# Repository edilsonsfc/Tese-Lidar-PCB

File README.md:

# Circuit Board (PCB) of Master's Thesis
This repository contains the circuit board project and supplementary materials related to my master's thesis.

## Table of Contents
- [Introduction](#introduction)
- [PCB](#pcb)
- [How to Use](#how-to-use)
- [Citation](#citation)

## Introduction
My master's thesis, titled "Three-dimensional mapping of an unknown environment based on a 2D laser measurement" explores the development of a low-cost 3D mapping system capable of generating a point cloud of an indoor environment and performing path planning. The work presented in this repository supports the findings and experiments conducted during the research process.
- [Hardware Structure](https://github.com/edilsonsfc/Tese-Lidar-Structure)
- [Printed Circuit Board](https://github.com/edilsonsfc/Tese-Lidar-PCB)
- [Control and Data Processing Algorithm](https://github.com/edilsonsfc/Tese-Lidar-Code)
- [Graphical User Interface](https://github.com/edilsonsfc/Tese-Lidar-GUI)

## PCB
This repository contains a collection of [...].

## How to Use

Feel free to explore and incorporate these models into your research or projects. Don't forget to cite this repository if you use the 3D models in your work.

## Citation
If you use the any material from this repository in your research or projects, please cite my master's thesis and this repository as follows:

- Master's Thesis: Ferreira, E. "Three-dimensional mapping of an unknown environment based on a 2D laser measurement" Instituto Politécnico de Bragança, 2023.
- Repository: https://github.com/edilsonsfc/Tese-Lidar-PCB

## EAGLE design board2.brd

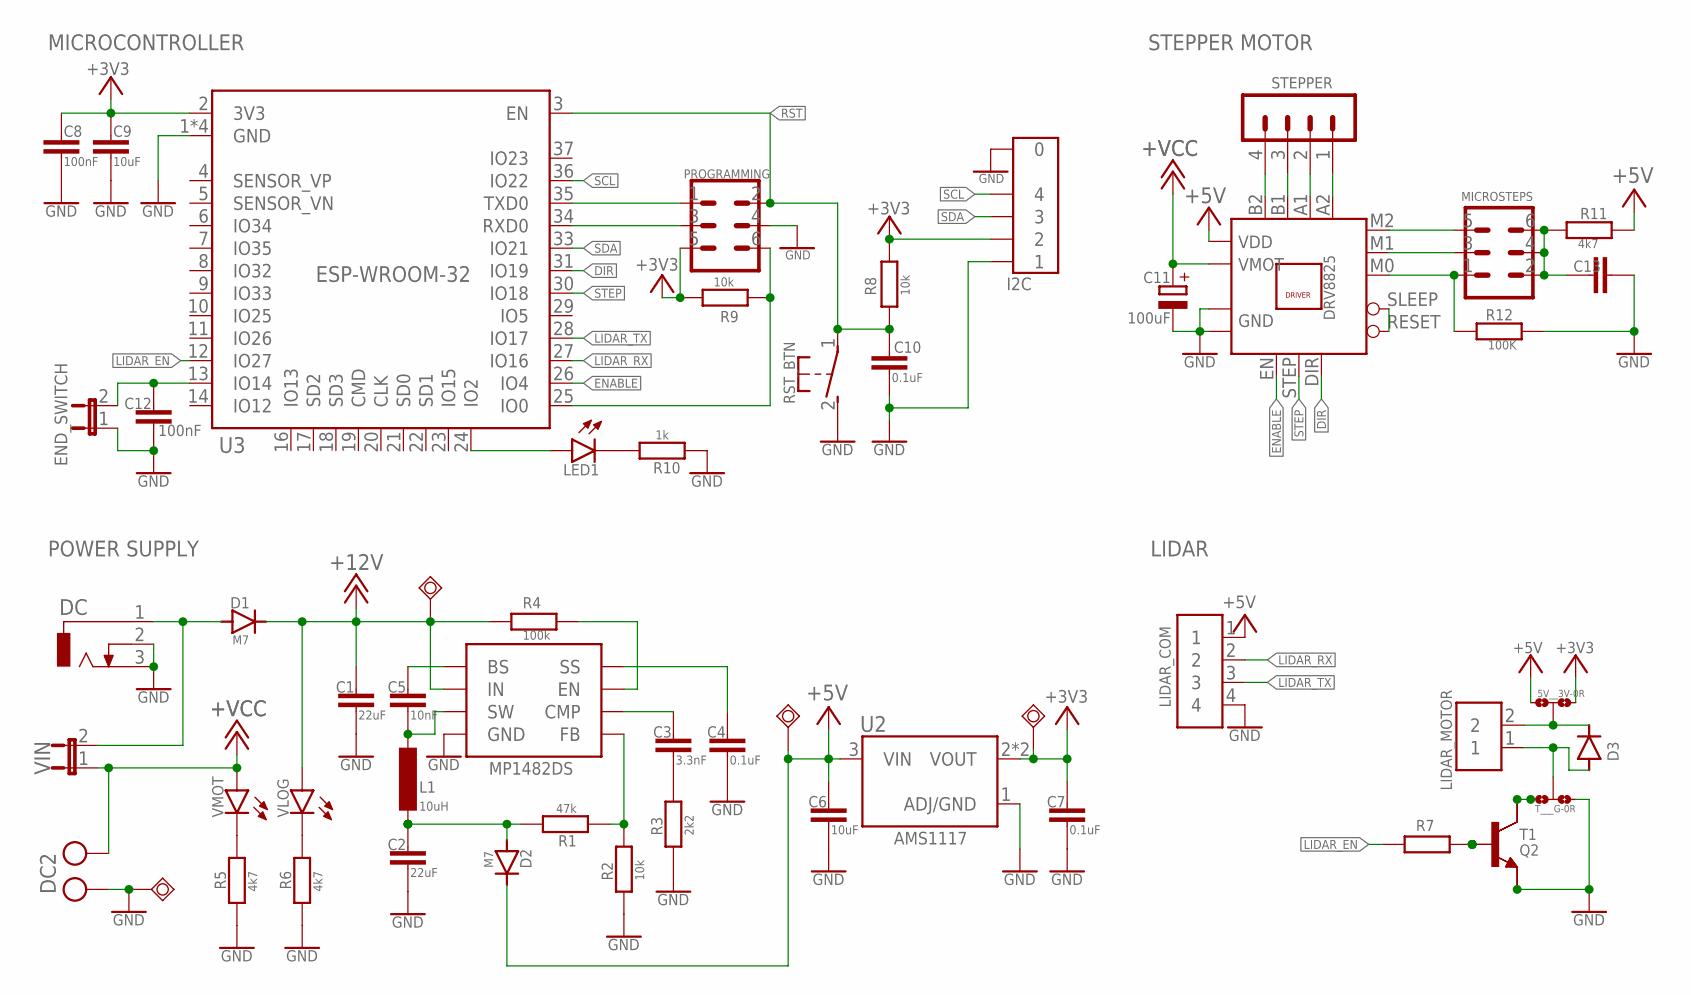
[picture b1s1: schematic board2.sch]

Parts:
3V3, 5V, 12V: TPSQTP07R; TP07R
5V__3V: 0R-JUMPA; A0R-JMP
C1, C2: 22uF; C1210K
C3: 3.3nF; C0805K
C4, C10: 0.1uF; C0805K
C5: 10nF; C0805K
C6, C9: 10uF; C1210K
C7: 0.1uF; C1210K
C8, C12: 100nF; C0805K
C11: 100uF; E3,5-8
C13: C-EUC0805K; C0805K
D1, D2, D3: M7; DO-214AC
DC: DCJ0202
DC2: DC2; AK500/2-H
DRIVER: DRV8825_PCB
DRV8825: DRV8825_H
END_SWITCH: END_SWITCH; JP1
GND: TPSQTP07R; TP07R
I2C: SM04B-SRSS-TB(LF)(SN); JST_SM04B-SRSS-TB(LF)(SN)
L1: 10uH; L5650M
LED1: 0; CHIP-LED0805
LIDAR_COM: 4PIN; B4B-PH-K-S
LIDAR_MOTOR: 2PIN; B2B-PH-K-S
MICROSTEPS: MicroSteps; MA03-2
PROGRAMMING: Programming; MA03-2
Q2: BC846ALT1SMD; SOT23
R1: 47k; R0805W
R2, R8, R9: 10k; R0805W
R3: 2k2; R0805W
R4: 100k; R0805W
R5, R6, R11: 4k7; R0805W
R7: R; R0805W
R10: 1k; R0805W
R12: 100K; R0805W
RST_BTN: DTSM-3
STEPPER: Stepper; MA04-1
T1: BD139_BCXXX; TO126+TO92
T___G: 0R-JUMPB; B0R-JMP
U1: MP1482DS; SOIC127P600X175-8N
U2: AMS1117; SOT229P700X180-4N
U3: ESP-WROOM-32
VIN: JUMPER; JP1
VLOG: 00; CHIP-LED0805
VMOT: 00; CHIP-LED0805

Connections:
+3V3: 3V3.TP, 5V__3V.1, 5V__3V.2, C7.1, C8.1, C9.1, D3.C, I2C.2, LIDAR_MOTOR.2, PROGRAMMING.5, R8.1, R9.2, U2.2 (VOUT), U2.4 (VOUT), U3.2 (3V3)
+5V: 5V.TP, 5V__3V.3, C6.2, D2.C, DRV8825.FAULT (VDD), LIDAR_COM.1, R11.2, U2.3 (VIN)
+12V: 12V.TP, C1.2, D1.C, R4.1, U1.2 (IN), VLOG.A
+VCC: C11.+, DC2.2, DRV8825.VMOT, DRV8825.VMOT1 (VMOT), VIN.1, VMOT.A
A1: DRV8825.A1, STEPPER.2
A2: DRV8825.A2, STEPPER.1
B1: DRV8825.B1, STEPPER.3
B2: DRV8825.B2, STEPPER.4
BS: C5.2, U1.1 (BS)
CMP: C3.2, U1.6 (CMP)
DIR: DRV8825.DIR, U3.31 (IO19)
EN: R4.2, U1.7 (EN)
ENABLE: DRV8825.EN, U3.26 (IO4)
END_SW: C12.2, END_SWITCH.2, U3.13 (IO14)
GND: C1.1, C2.2, C4.1, C6.1, C7.2, C8.2, C9.2, C10.2, C11.-, C12.1, C13.2, DC.2, DC.3, DC2.1, DRV8825.GND, DRV8825.GND1 (GMOT), END_SWITCH.1, GND.TP, I2C.1, I2C.S1 (0), I2C.S2 (0), LIDAR_COM.4, PROGRAMMING.4, Q2.2 (E), R2.1, R3.1, R5.1, R6.1, R10.1, R12.1, RST_BTN.2, T1.E, T1.E1 (E), T___G.3, U1.4 (GND), U2.1 (ADJ/GND), U3.1 (GND), U3.15 (GND), U3.38 (GND), U3.GND
IO0: PROGRAMMING.6, R9.1, U3.25 (IO0)
IO2: LED1.A, U3.24 (IO2)
LIDAR_EN: R7.1, U3.12 (IO27)
LIDAR_RX: LIDAR_COM.2, U3.27 (IO16)
LIDAR_TX: LIDAR_COM.3, U3.28 (IO17)
M0: DRV8825.M0, MICROSTEPS.1, R12.2
M1: DRV8825.M1, MICROSTEPS.3
M2: DRV8825.M2, MICROSTEPS.5
MT: D3.A, LIDAR_MOTOR.1, T___G.2
unnamed: C2.1, D2.A, L1.1, R1.1
unnamed: C3.1, R3.2
unnamed: R5.2, VMOT.C
unnamed: Q2.3 (C), T1.C, T___G.1
unnamed: C13.1, MICROSTEPS.2, MICROSTEPS.4, MICROSTEPS.6, R11.1
unnamed: LED1.C, R10.2
unnamed: R6.2, VLOG.C
unnamed: R1.2, R2.2, U1.5 (FB)
unnamed: DRV8825.RESET, DRV8825.SLEEP
unnamed: Q2.1 (B), R7.2, T1.B
RST: C10.1, PROGRAMMING.2, R8.2, RST_BTN.1, U3.3 (EN)
RXD: PROGRAMMING.3, U3.34 (RXD0)
SCL: I2C.4, U3.36 (IO22)
SDA: I2C.3, U3.33 (IO21)
SS: C4.2, U1.8 (SS)
STEP: DRV8825.STEP, U3.30 (IO18)
SW: C5.1, L1.2, U1.3 (SW)
TXD: PROGRAMMING.1, U3.35 (TXD0)
VIN: D1.A, DC.1, VIN.2

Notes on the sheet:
MICROCONTROLLER
STEPPER MOTOR
LIDAR
POWER SUPPLY

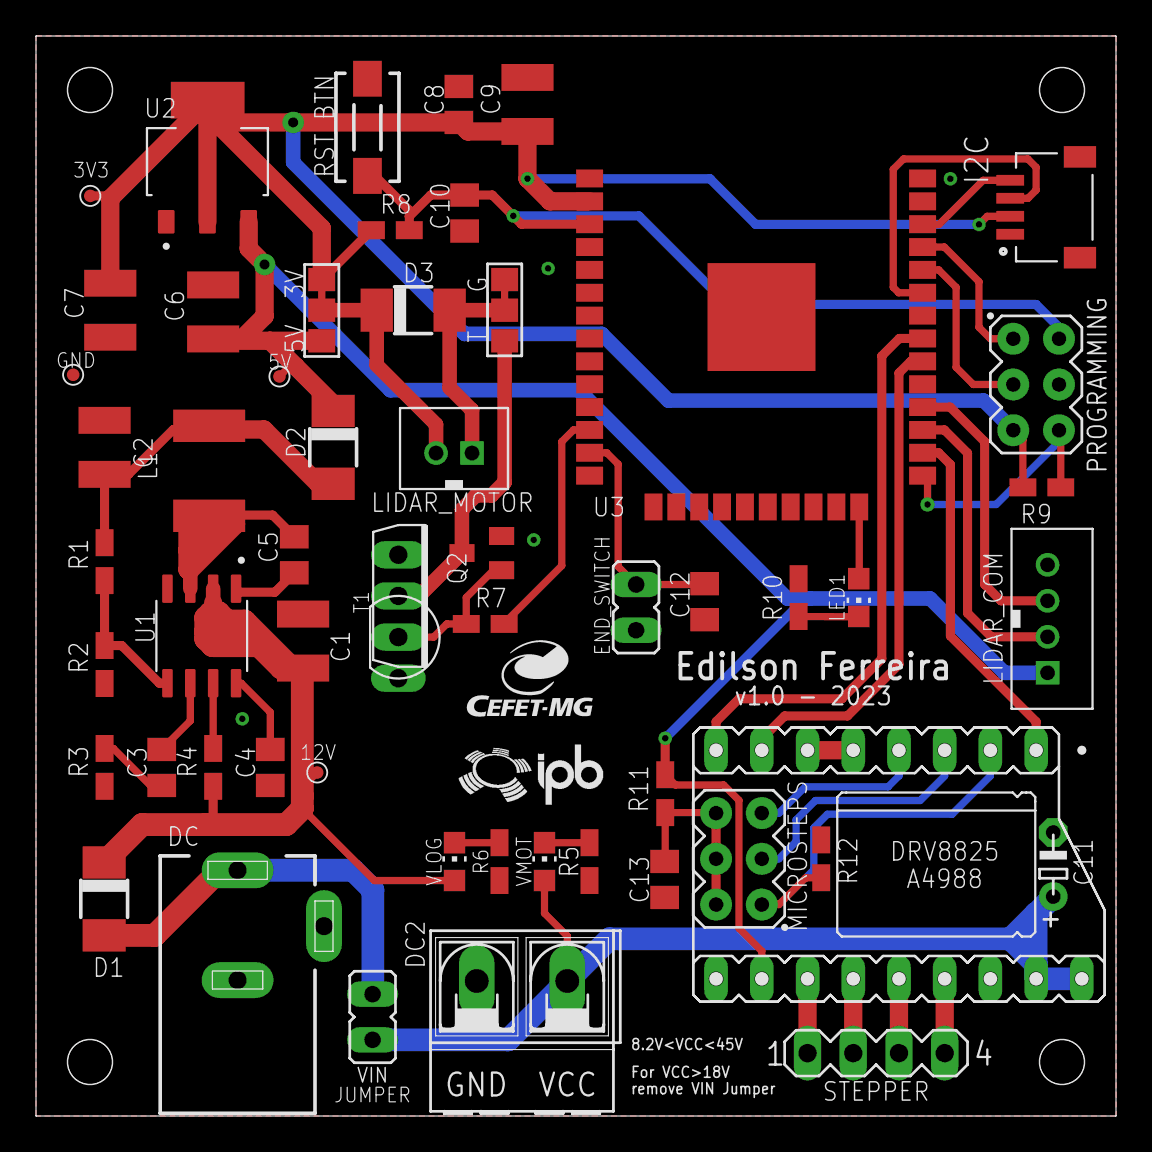
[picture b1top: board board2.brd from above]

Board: 2 copper layers, 59.9 x 59.9 mm, 56 parts (0 on the bottom side), 43 nets.

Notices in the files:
parts and their libraries:
esp32_smd: Creative Commons Attribution-ShareAlike 4.0 International
